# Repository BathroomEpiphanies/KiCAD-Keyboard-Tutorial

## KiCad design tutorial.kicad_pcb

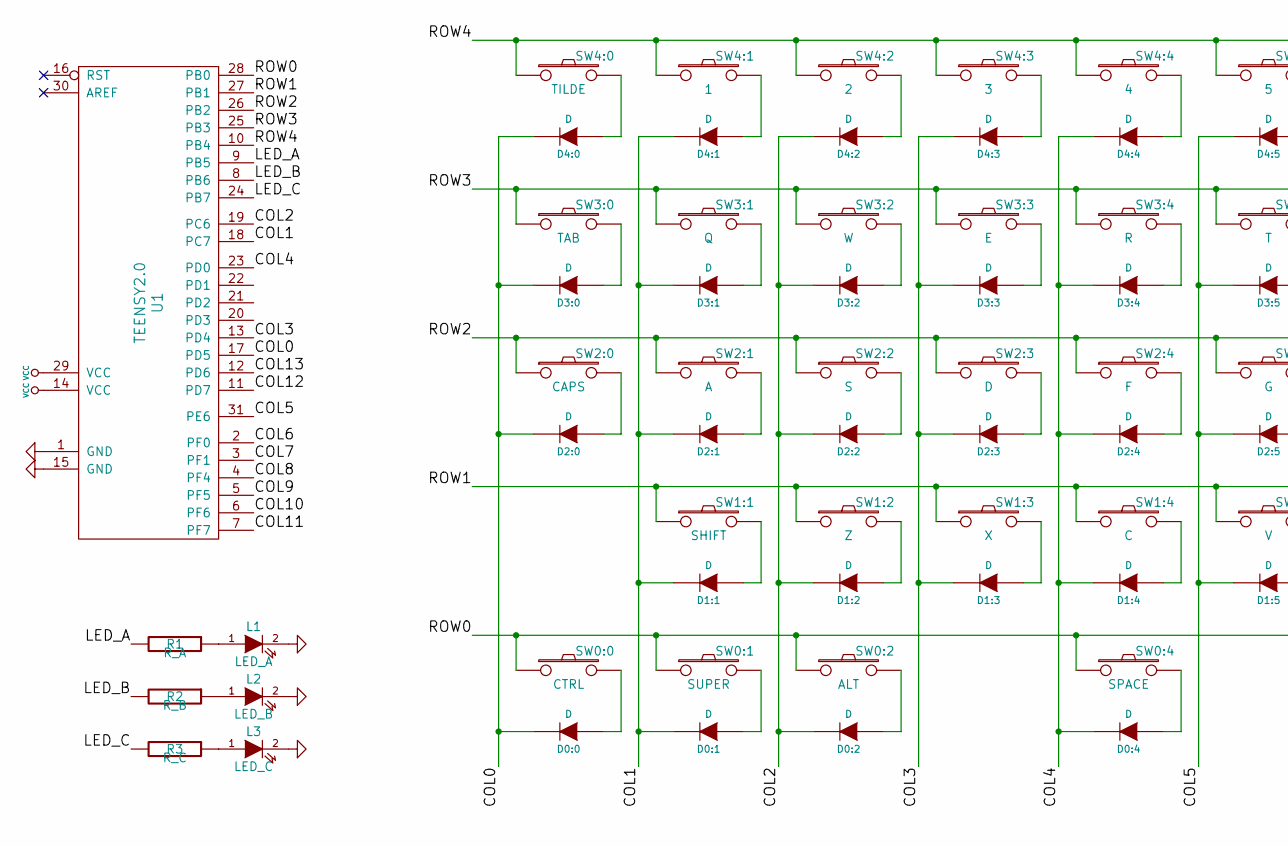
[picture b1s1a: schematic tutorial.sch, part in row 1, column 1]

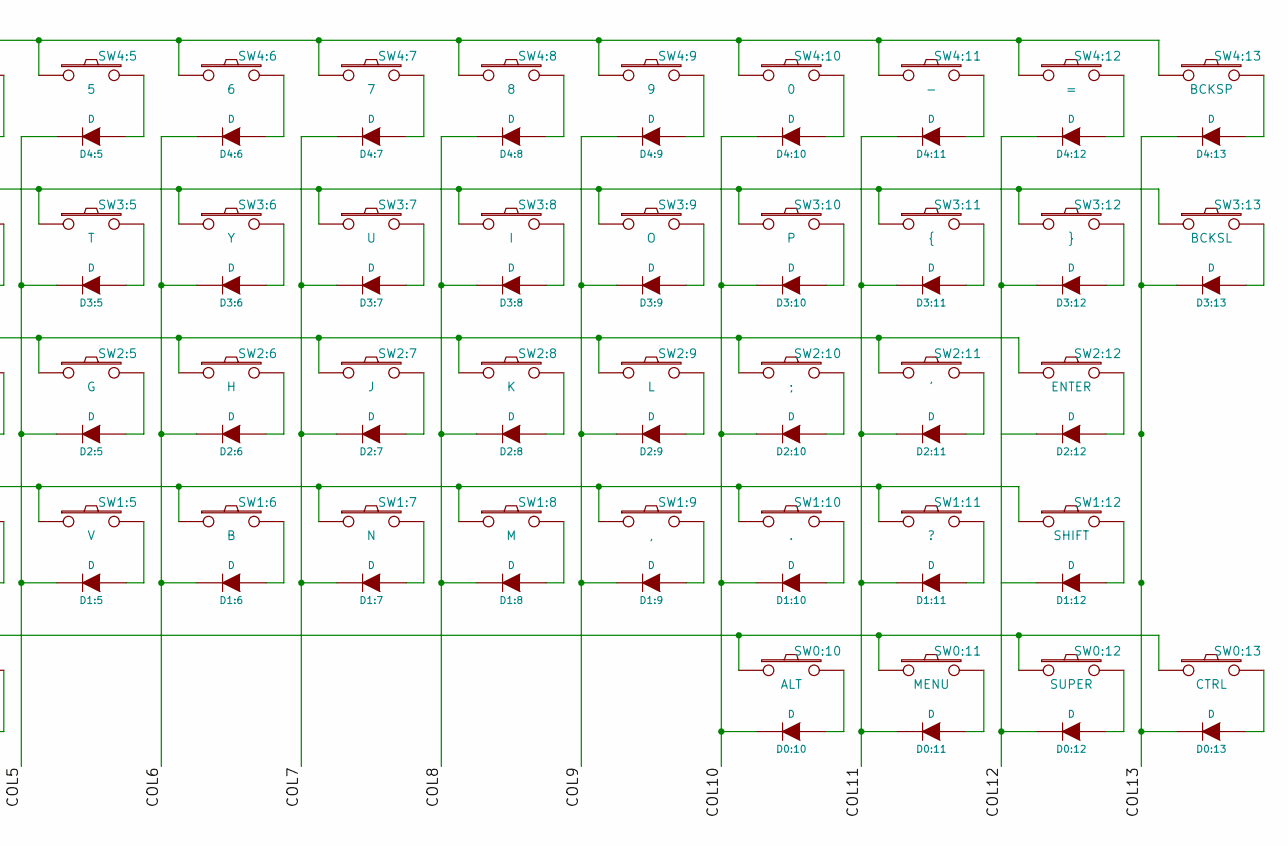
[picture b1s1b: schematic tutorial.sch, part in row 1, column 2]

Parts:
D0:0, D0:1, D0:2, D0:4, D0:10, D0:11, D0:12, D0:13, D1:1, D1:2, D1:3, D1:4, D1:5, D1:6, D1:7, D1:8, D1:9, D1:10, D1:11, D1:12, D2:0, D2:1, D2:2, D2:3, D2:4, D2:5, D2:6, D2:7, D2:8, D2:9, D2:10, D2:11, D2:12, D3:0, D3:1, D3:2, D3:3, D3:4, D3:5, D3:6, D3:7, D3:8, D3:9, D3:10, D3:11, D3:12, D3:13, D4:0, D4:1, D4:2, D4:3, D4:4, D4:5, D4:6, D4:7, D4:8, D4:9, D4:10, D4:11, D4:12, D4:13: D; DIODE
L1: LED_A; CHERRY_MX_LED
L2: LED_B; CHERRY_MX_LED
L3: LED_C; CHERRY_MX_LED
R1: R_A; RESISTOR
R2: R_B; RESISTOR
R3: R_C; RESISTOR
SW0:0, SW0:13: CTRL; CHERRY_PCB_125H
SW0:1, SW0:12: SUPER; CHERRY_PCB_125H
SW0:2, SW0:10: ALT; CHERRY_PCB_125H
SW0:4: SPACE; CHERRY_PCB_625H
SW0:11: MENU; CHERRY_PCB_125H
SW1:1: SHIFT; CHERRY_PCB_225H
SW1:2: Z; CHERRY_PCB_100H
SW1:3: X; CHERRY_PCB_100H
SW1:4: C; CHERRY_PCB_100H
SW1:5: V; CHERRY_PCB_100H
SW1:6: B; CHERRY_PCB_100H
SW1:7: N; CHERRY_PCB_100H
SW1:8: M; CHERRY_PCB_100H
SW1:9: ,; CHERRY_PCB_100H
SW1:10: .; CHERRY_PCB_100H
SW1:11: ?; CHERRY_PCB_100H
SW1:12: SHIFT; CHERRY_PCB_275H
SW2:0: CAPS; CHERRY_PCB_175H
SW2:1: A; CHERRY_PCB_100H
SW2:2: S; CHERRY_PCB_100H
SW2:3: D; CHERRY_PCB_100H
SW2:4: F; CHERRY_PCB_100H
SW2:5: G; CHERRY_PCB_100H
SW2:6: H; CHERRY_PCB_100H
SW2:7: J; CHERRY_PCB_100H
SW2:8: K; CHERRY_PCB_100H
SW2:9: L; CHERRY_PCB_100H
SW2:10: ;; CHERRY_PCB_100H
SW2:11: '; CHERRY_PCB_100H
SW2:12: ENTER; CHERRY_PCB_225H
SW3:0: TAB; CHERRY_PCB_150H
SW3:1: Q; CHERRY_PCB_100H
SW3:2: W; CHERRY_PCB_100H
SW3:3: E; CHERRY_PCB_100H
SW3:4: R; CHERRY_PCB_100H
SW3:5: T; CHERRY_PCB_100H
SW3:6: Y; CHERRY_PCB_100H
SW3:7: U; CHERRY_PCB_100H
SW3:8: I; CHERRY_PCB_100H
SW3:9: O; CHERRY_PCB_100H
SW3:10: P; CHERRY_PCB_100H
SW3:11: {; CHERRY_PCB_100H
SW3:12: }; CHERRY_PCB_100H
SW3:13: BCKSL; CHERRY_PCB_150H
SW4:0: TILDE; CHERRY_PCB_100H
SW4:1: 1; CHERRY_PCB_100H
SW4:2: 2; CHERRY_PCB_100H
SW4:3: 3; CHERRY_PCB_100H
SW4:4: 4; CHERRY_PCB_100H
SW4:5: 5; CHERRY_PCB_100H
SW4:6: 6; CHERRY_PCB_100H
SW4:7: 7; CHERRY_PCB_100H
SW4:8: 8; CHERRY_PCB_100H
SW4:9: 9; CHERRY_PCB_100H
SW4:10: 0; CHERRY_PCB_100H
SW4:11: -; CHERRY_PCB_100H
SW4:12: =; CHERRY_PCB_100H
SW4:13: BCKSP; CHERRY_PCB_200H
U1: TEENSY2.0; TEENSY_2.0

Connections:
/COL0: D0:0.2 (K), D2:0.2 (K), D3:0.2 (K), D4:0.2 (K), U1.17 (PD5)
/COL1: D0:1.2 (K), D1:1.2 (K), D2:1.2 (K), D3:1.2 (K), D4:1.2 (K), U1.18 (PC7)
/COL2: D0:2.2 (K), D1:2.2 (K), D2:2.2 (K), D3:2.2 (K), D4:2.2 (K), U1.19 (PC6)
/COL3: D1:3.2 (K), D2:3.2 (K), D3:3.2 (K), D4:3.2 (K), U1.13 (PD4)
/COL4: D0:4.2 (K), D1:4.2 (K), D2:4.2 (K), D3:4.2 (K), D4:4.2 (K), U1.23 (PD0)
/COL5: D1:5.2 (K), D2:5.2 (K), D3:5.2 (K), D4:5.2 (K), U1.31 (PE6)
/COL6: D1:6.2 (K), D2:6.2 (K), D3:6.2 (K), D4:6.2 (K), U1.2 (PF0)
/COL7: D1:7.2 (K), D2:7.2 (K), D3:7.2 (K), D4:7.2 (K), U1.3 (PF1)
/COL8: D1:8.2 (K), D2:8.2 (K), D3:8.2 (K), D4:8.2 (K), U1.4 (PF4)
/COL9: D1:9.2 (K), D2:9.2 (K), D3:9.2 (K), D4:9.2 (K), U1.5 (PF5)
/COL10: D0:10.2 (K), D1:10.2 (K), D2:10.2 (K), D3:10.2 (K), D4:10.2 (K), U1.6 (PF6)
/COL11: D0:11.2 (K), D1:11.2 (K), D2:11.2 (K), D3:11.2 (K), D4:11.2 (K), U1.7 (PF7)
/COL12: D0:12.2 (K), D3:12.2 (K), D4:12.2 (K), U1.11 (PD7)
/COL13: D0:13.2 (K), D3:13.2 (K), D4:13.2 (K), U1.12 (PD6)
/LED_A: R1.2, U1.9 (PB5)
/LED_B: R2.2, U1.8 (PB6)
/LED_C: R3.2, U1.24 (PB7)
/ROW0: SW0:0.1, SW0:1.1, SW0:2.1, SW0:4.1, SW0:10.1, SW0:11.1, SW0:12.1, SW0:13.1, U1.28 (PB0)
/ROW1: SW1:1.1, SW1:2.1, SW1:3.1, SW1:4.1, SW1:5.1, SW1:6.1, SW1:7.1, SW1:8.1, SW1:9.1, SW1:10.1, SW1:11.1, SW1:12.1, U1.27 (PB1)
/ROW2: SW2:0.1, SW2:1.1, SW2:2.1, SW2:3.1, SW2:4.1, SW2:5.1, SW2:6.1, SW2:7.1, SW2:8.1, SW2:9.1, SW2:10.1, SW2:11.1, SW2:12.1, U1.26 (PB2)
/ROW3: SW3:0.1, SW3:1.1, SW3:2.1, SW3:3.1, SW3:4.1, SW3:5.1, SW3:6.1, SW3:7.1, SW3:8.1, SW3:9.1, SW3:10.1, SW3:11.1, SW3:12.1, SW3:13.1, U1.25 (PB3)
/ROW4: SW4:0.1, SW4:1.1, SW4:2.1, SW4:3.1, SW4:4.1, SW4:5.1, SW4:6.1, SW4:7.1, SW4:8.1, SW4:9.1, SW4:10.1, SW4:11.1, SW4:12.1, SW4:13.1, U1.10 (PB4)
GND: L1.2 (K), L2.2 (K), L3.2 (K), U1.1 (GND), U1.15 (GND)
unnamed: D0:0.1 (A), SW0:0.2
unnamed: D0:1.1 (A), SW0:1.2
unnamed: D0:2.1 (A), SW0:2.2
unnamed: D0:4.1 (A), SW0:4.2
unnamed: D0:10.1 (A), SW0:10.2
unnamed: D0:11.1 (A), SW0:11.2
unnamed: D0:12.1 (A), SW0:12.2
unnamed: D0:13.1 (A), SW0:13.2
unnamed: D1:1.1 (A), SW1:1.2
unnamed: D1:2.1 (A), SW1:2.2
unnamed: D1:3.1 (A), SW1:3.2
unnamed: D1:4.1 (A), SW1:4.2
unnamed: D1:5.1 (A), SW1:5.2
unnamed: D1:6.1 (A), SW1:6.2
unnamed: D1:7.1 (A), SW1:7.2
unnamed: D1:8.1 (A), SW1:8.2
unnamed: D1:9.1 (A), SW1:9.2
unnamed: D1:10.1 (A), SW1:10.2
unnamed: D1:11.1 (A), SW1:11.2
unnamed: D1:12.1 (A), SW1:12.2
unnamed: D2:0.1 (A), SW2:0.2
unnamed: D2:1.1 (A), SW2:1.2
unnamed: D2:2.1 (A), SW2:2.2
unnamed: D2:3.1 (A), SW2:3.2
unnamed: D2:4.1 (A), SW2:4.2
unnamed: D2:5.1 (A), SW2:5.2
unnamed: D2:6.1 (A), SW2:6.2
unnamed: D2:7.1 (A), SW2:7.2
unnamed: D2:8.1 (A), SW2:8.2
unnamed: D2:9.1 (A), SW2:9.2
unnamed: D2:10.1 (A), SW2:10.2
unnamed: D2:11.1 (A), SW2:11.2
unnamed: D2:12.1 (A), SW2:12.2
unnamed: D3:0.1 (A), SW3:0.2
unnamed: D3:1.1 (A), SW3:1.2
unnamed: D3:2.1 (A), SW3:2.2
unnamed: D3:3.1 (A), SW3:3.2
unnamed: D3:4.1 (A), SW3:4.2
unnamed: D3:5.1 (A), SW3:5.2
unnamed: D3:6.1 (A), SW3:6.2
unnamed: D3:7.1 (A), SW3:7.2
unnamed: D3:8.1 (A), SW3:8.2
unnamed: D3:9.1 (A), SW3:9.2
unnamed: D3:10.1 (A), SW3:10.2
unnamed: D3:11.1 (A), SW3:11.2
unnamed: D3:12.1 (A), SW3:12.2
unnamed: D3:13.1 (A), SW3:13.2
unnamed: D4:0.1 (A), SW4:0.2
unnamed: D4:1.1 (A), SW4:1.2
unnamed: D4:2.1 (A), SW4:2.2
unnamed: D4:3.1 (A), SW4:3.2
unnamed: D4:4.1 (A), SW4:4.2
unnamed: D4:5.1 (A), SW4:5.2
unnamed: D4:6.1 (A), SW4:6.2
unnamed: D4:7.1 (A), SW4:7.2
unnamed: D4:8.1 (A), SW4:8.2
unnamed: D4:9.1 (A), SW4:9.2
unnamed: D4:10.1 (A), SW4:10.2
unnamed: D4:11.1 (A), SW4:11.2
unnamed: D4:12.1 (A), SW4:12.2
unnamed: D4:13.1 (A), SW4:13.2
unnamed: L1.1 (A), R1.1
unnamed: L2.1 (A), R2.1
unnamed: L3.1 (A), R3.1
VCC: U1.14 (VCC), U1.29 (VCC)

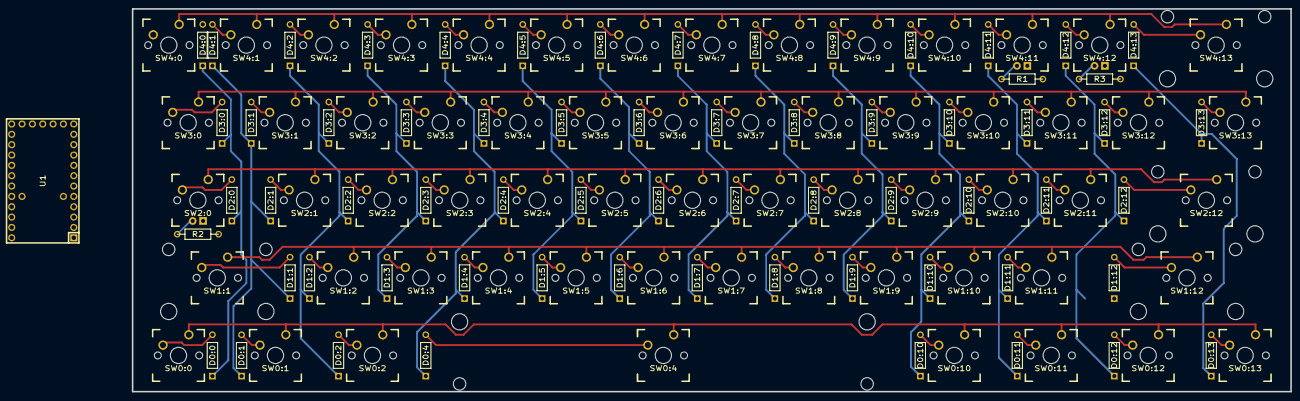
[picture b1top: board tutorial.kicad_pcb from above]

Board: 2 copper layers, 284.5 x 94.0 mm, 129 parts (0 on the bottom side), 88 nets.

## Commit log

2014-05-03 fix spelling of module name
2014-05-03 copy CHERRY_MX_DIODE from board to footprints module
2014-05-03 restore Makefile from 61c2fa8d53c15bd6494044e66afc824ccee749eb
2016-08-25 Updated to "new" KiCAD formats
2016-08-25 Deleted stuff
2016-08-25 Forgot to save file
2016-11-10 Added ISO enter and Stepped 1.75u
2016-11-10 Added the darned license
2016-11-10 There, fixed that for you..
